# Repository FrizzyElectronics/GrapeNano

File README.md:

# GrapeNano
A Arduino Nano Compatible from Frizzy

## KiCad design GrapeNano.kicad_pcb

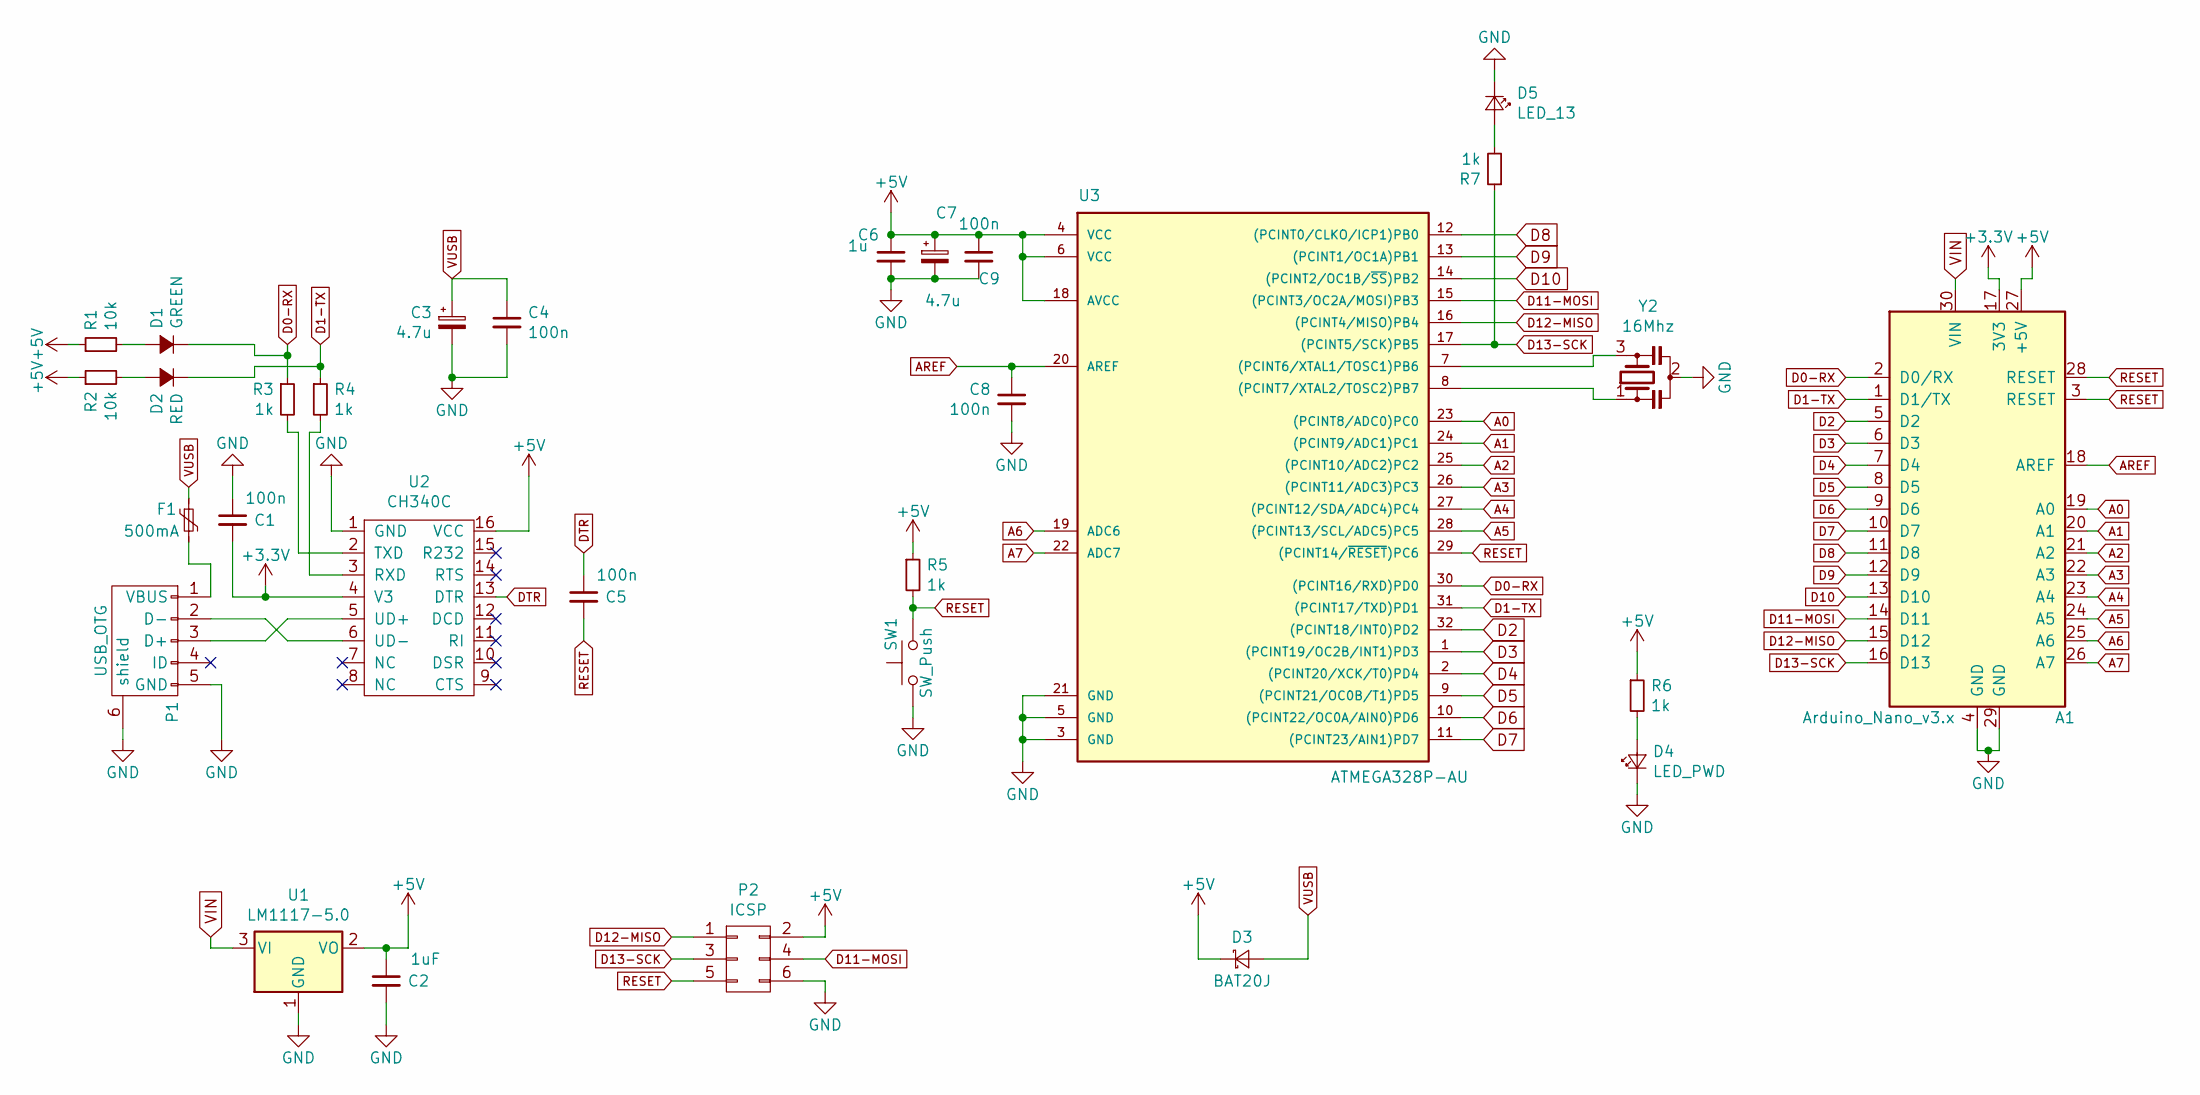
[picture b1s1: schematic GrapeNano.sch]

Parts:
A1: Arduino_Nano_v3.x; Arduino_Nano_WithMountingHoles
C1, C4, C5, C8, C9: 100n; C_0603
C2: 1uF; C_0603
C3, C7: 4.7u; CP_Tantalum_Case-A_EIA-3216-18_Reflow
C6: 1u; C_0603
D1: GREEN; LED_0805
D2: RED; LED_0805
D3: BAT20J; D_SOD-323
D4: LED_PWD; LED_0805
D5: LED_13; LED_0805
F1: 500mA; C_0603_HandSoldering
P1: USB_OTG; USB_Micro-B_Molex-105017-0001
P2: ICSP; 2X3
R1, R2: 10k; R_0603
R3, R4, R5, R6, R7: 1k; R_0603
SW1: SW_Push; SW_SPST_B3U-1000P
U1: LM1117-5.0; SOT-223
U2: CH340C; SOIC-16_3.9x9.9mm_Pitch1.27mm
U3: ATMEGA328P-AU; TQFP-32_7x7mm_Pitch0.8mm
Y2: 16Mhz; RESONATOR-SMD-3.2X1.3

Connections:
+3V3: A1.17 (3V3), C1.2, U2.4 (V3)
+5V: A1.27 (+5V), C2.1, C6.1, C7.1, C9.1, D3.1 (K), P2.2, R1.1, R2.1, R5.1, R6.1, U1.2 (VO), U2.16 (VCC), U3.4 (VCC), U3.6 (VCC), U3.18 (AVCC)
A0: A1.19 (A0), U3.23 ((PCINT8/ADC0)PC0)
A1: A1.20 (A1), U3.24 ((PCINT9/ADC1)PC1)
A2: A1.21 (A2), U3.25 ((PCINT10/ADC2)PC2)
A3: A1.22 (A3), U3.26 ((PCINT11/ADC3)PC3)
A4: A1.23 (A4), U3.27 ((PCINT12/SDA/ADC4)PC4)
A5: A1.24 (A5), U3.28 ((PCINT13/SCL/ADC5)PC5)
A6: A1.25 (A6), U3.19 (ADC6)
A7: A1.26 (A7), U3.22 (ADC7)
AREF: A1.18 (AREF), C8.1, U3.20 (AREF)
D0-RX: A1.2 (D0/RX), D1.1 (K), R3.1, U3.30 ((PCINT16/RXD)PD0)
D1-TX: A1.1 (D1/TX), D2.1 (K), R4.1, U3.31 ((PCINT17/TXD)PD1)
D2: A1.5 (D2), U3.32 ((PCINT18/INT0)PD2)
D3: A1.6 (D3), U3.1 ((PCINT19/OC2B/INT1)PD3)
D4: A1.7 (D4), U3.2 ((PCINT20/XCK/T0)PD4)
D5: A1.8 (D5), U3.9 ((PCINT21/OC0B/T1)PD5)
D6: A1.9 (D6), U3.10 ((PCINT22/OC0A/AIN0)PD6)
D7: A1.10 (D7), U3.11 ((PCINT23/AIN1)PD7)
D8: A1.11 (D8), U3.12 ((PCINT0/CLKO/ICP1)PB0)
D9: A1.12 (D9), U3.13 ((PCINT1/OC1A)PB1)
D10: A1.13 (D10), U3.14 ((PCINT2/OC1B/~SS~)PB2)
D11-MOSI: A1.14 (D11), P2.4, U3.15 ((PCINT3/OC2A/MOSI)PB3)
D12-MISO: A1.15 (D12), P2.1, U3.16 ((PCINT4/MISO)PB4)
D13-SCK: A1.16 (D13), P2.3, R7.1, U3.17 ((PCINT5/SCK)PB5)
DTR: C5.1, U2.13 (DTR)
GND: A1.4 (GND), A1.29 (GND), C1.1, C2.2, C3.2, C4.2, C6.2, C7.2, C8.2, C9.2, D4.1 (K), D5.1 (K), P1.5 (GND), P1.6 (shield), P2.6, SW1.1, U1.1 (GND), U2.1 (GND), U3.3 (GND), U3.5 (GND), U3.21 (GND), Y2.2
unnamed: D1.2 (A), R1.2
unnamed: D2.2 (A), R2.2
unnamed: D4.2 (A), R6.2
unnamed: D5.2 (A), R7.2
unnamed: F1.2, P1.1 (VBUS)
unnamed: P1.2 (D-), U2.6 (UD-)
unnamed: P1.3 (D+), U2.5 (UD+)
unnamed: R3.2, U2.2 (TXD)
unnamed: R4.2, U2.3 (RXD)
unnamed: U3.7 ((PCINT6/XTAL1/TOSC1)PB6), Y2.3
unnamed: U3.8 ((PCINT7/XTAL2/TOSC2)PB7), Y2.1
RESET: A1.3 (RESET), A1.28 (RESET), C5.2, P2.5, R5.2, SW1.2, U3.29 ((PCINT14/~RESET~)PC6)
VIN: A1.30 (VIN), U1.3 (VI)
VUSB: C3.1, C4.1, D3.2 (A), F1.1

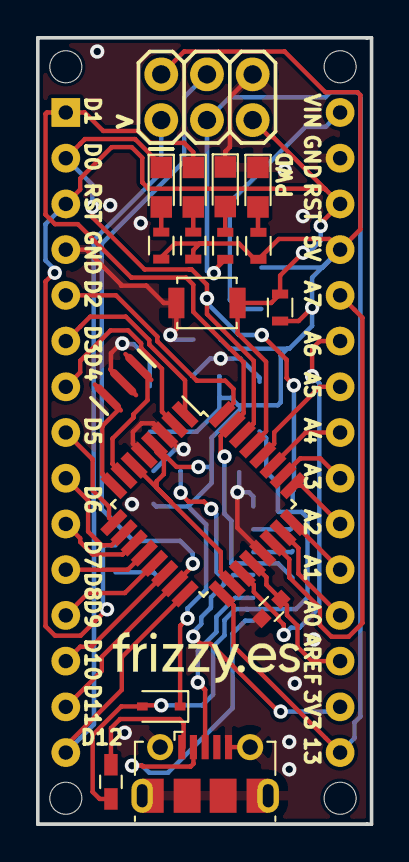
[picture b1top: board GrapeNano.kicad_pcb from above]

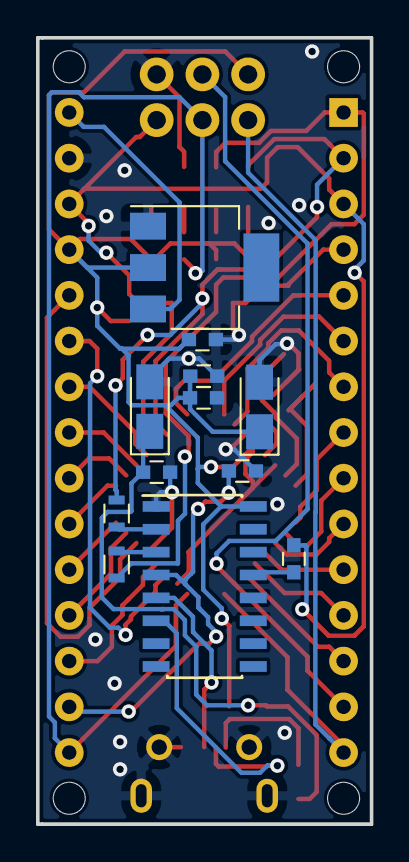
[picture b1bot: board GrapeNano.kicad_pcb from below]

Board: 2 copper layers, 18.5 x 43.7 mm, 30 parts (12 on the bottom side), 41 nets.

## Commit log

2017-01-30 Starting the schematic
2019-02-25 Haciendo el esquema
2019-02-27 Esquema terminado
2019-02-28 Componentes colocados y comenzando a enrutar
2019-03-01 Enrutando
2019-03-01 4 nets
2019-03-02 1 net
2019-03-02 Enrutado completo
2019-03-02 Mandada a fábrica
2019-04-24 CH340G cambiado por CH340C
2019-06-17 mandado a fabrica
2019-06-22 Errores corregidos y mandado a fábrica
    Corto en el condensador C1 y U3 sin alimentación
